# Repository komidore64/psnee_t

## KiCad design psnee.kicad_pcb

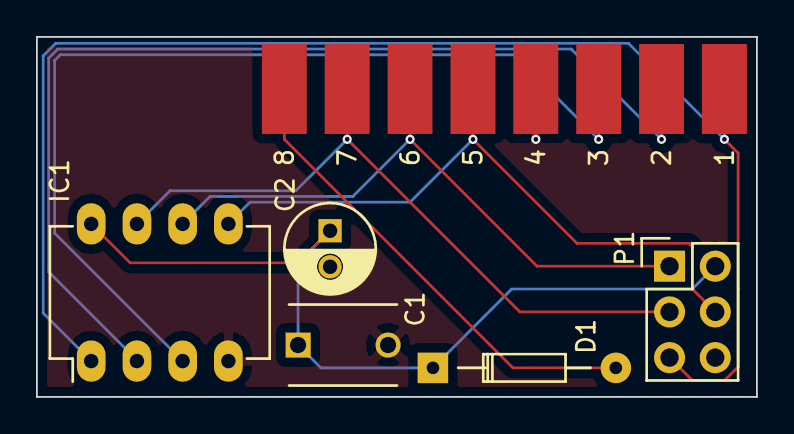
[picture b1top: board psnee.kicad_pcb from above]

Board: 2 copper layers, 40.0 x 20.0 mm, 13 parts (0 on the bottom side), 9 nets.

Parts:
1, 2, 3, 4, 5, 6, 7, 8: wire_pad_2.5_5mm_single
C1: 100nF; C_Disc_D6_P5
C2: 100uF; C_Radial_D5_L11_P2
D1: D; Diode_DO-35_SOD27_Horizontal_RM10
IC1: attiny45; DIP-8_W7.62mm_LongPads
P1: header; Pin_Header_Straight_2x03

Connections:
/1: 1.1, IC1.1, P1.5
/2: 2.1, IC1.2
/3: 3.1, IC1.3
/5: 5.1, IC1.5, P1.4
/6: 6.1, IC1.6, P1.1
/7: 7.1, IC1.7, P1.3
GND: 4.1, C1.2, C2.2, IC1.4, P1.6
unnamed: C1.1, C2.1, D1.1, IC1.8, P1.2
VCC: 8.1, D1.2

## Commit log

2017-11-19 psnee_t - first oshpark fab
2018-01-06 updated schematic for v2.0
    - added decoupling capacitors
    - regenerated annotations
    - associated footprints to components
    - regenerated netlist
2018-03-01 pcb for v2.0
2018-03-01 add CERN OHL license
2018-03-14 added text for pcb v2
2018-03-18 add oshw logo
2018-03-18 generate v2 gerbers and drill
2018-03-18 update for_oshpark gerbers with proper extentions
